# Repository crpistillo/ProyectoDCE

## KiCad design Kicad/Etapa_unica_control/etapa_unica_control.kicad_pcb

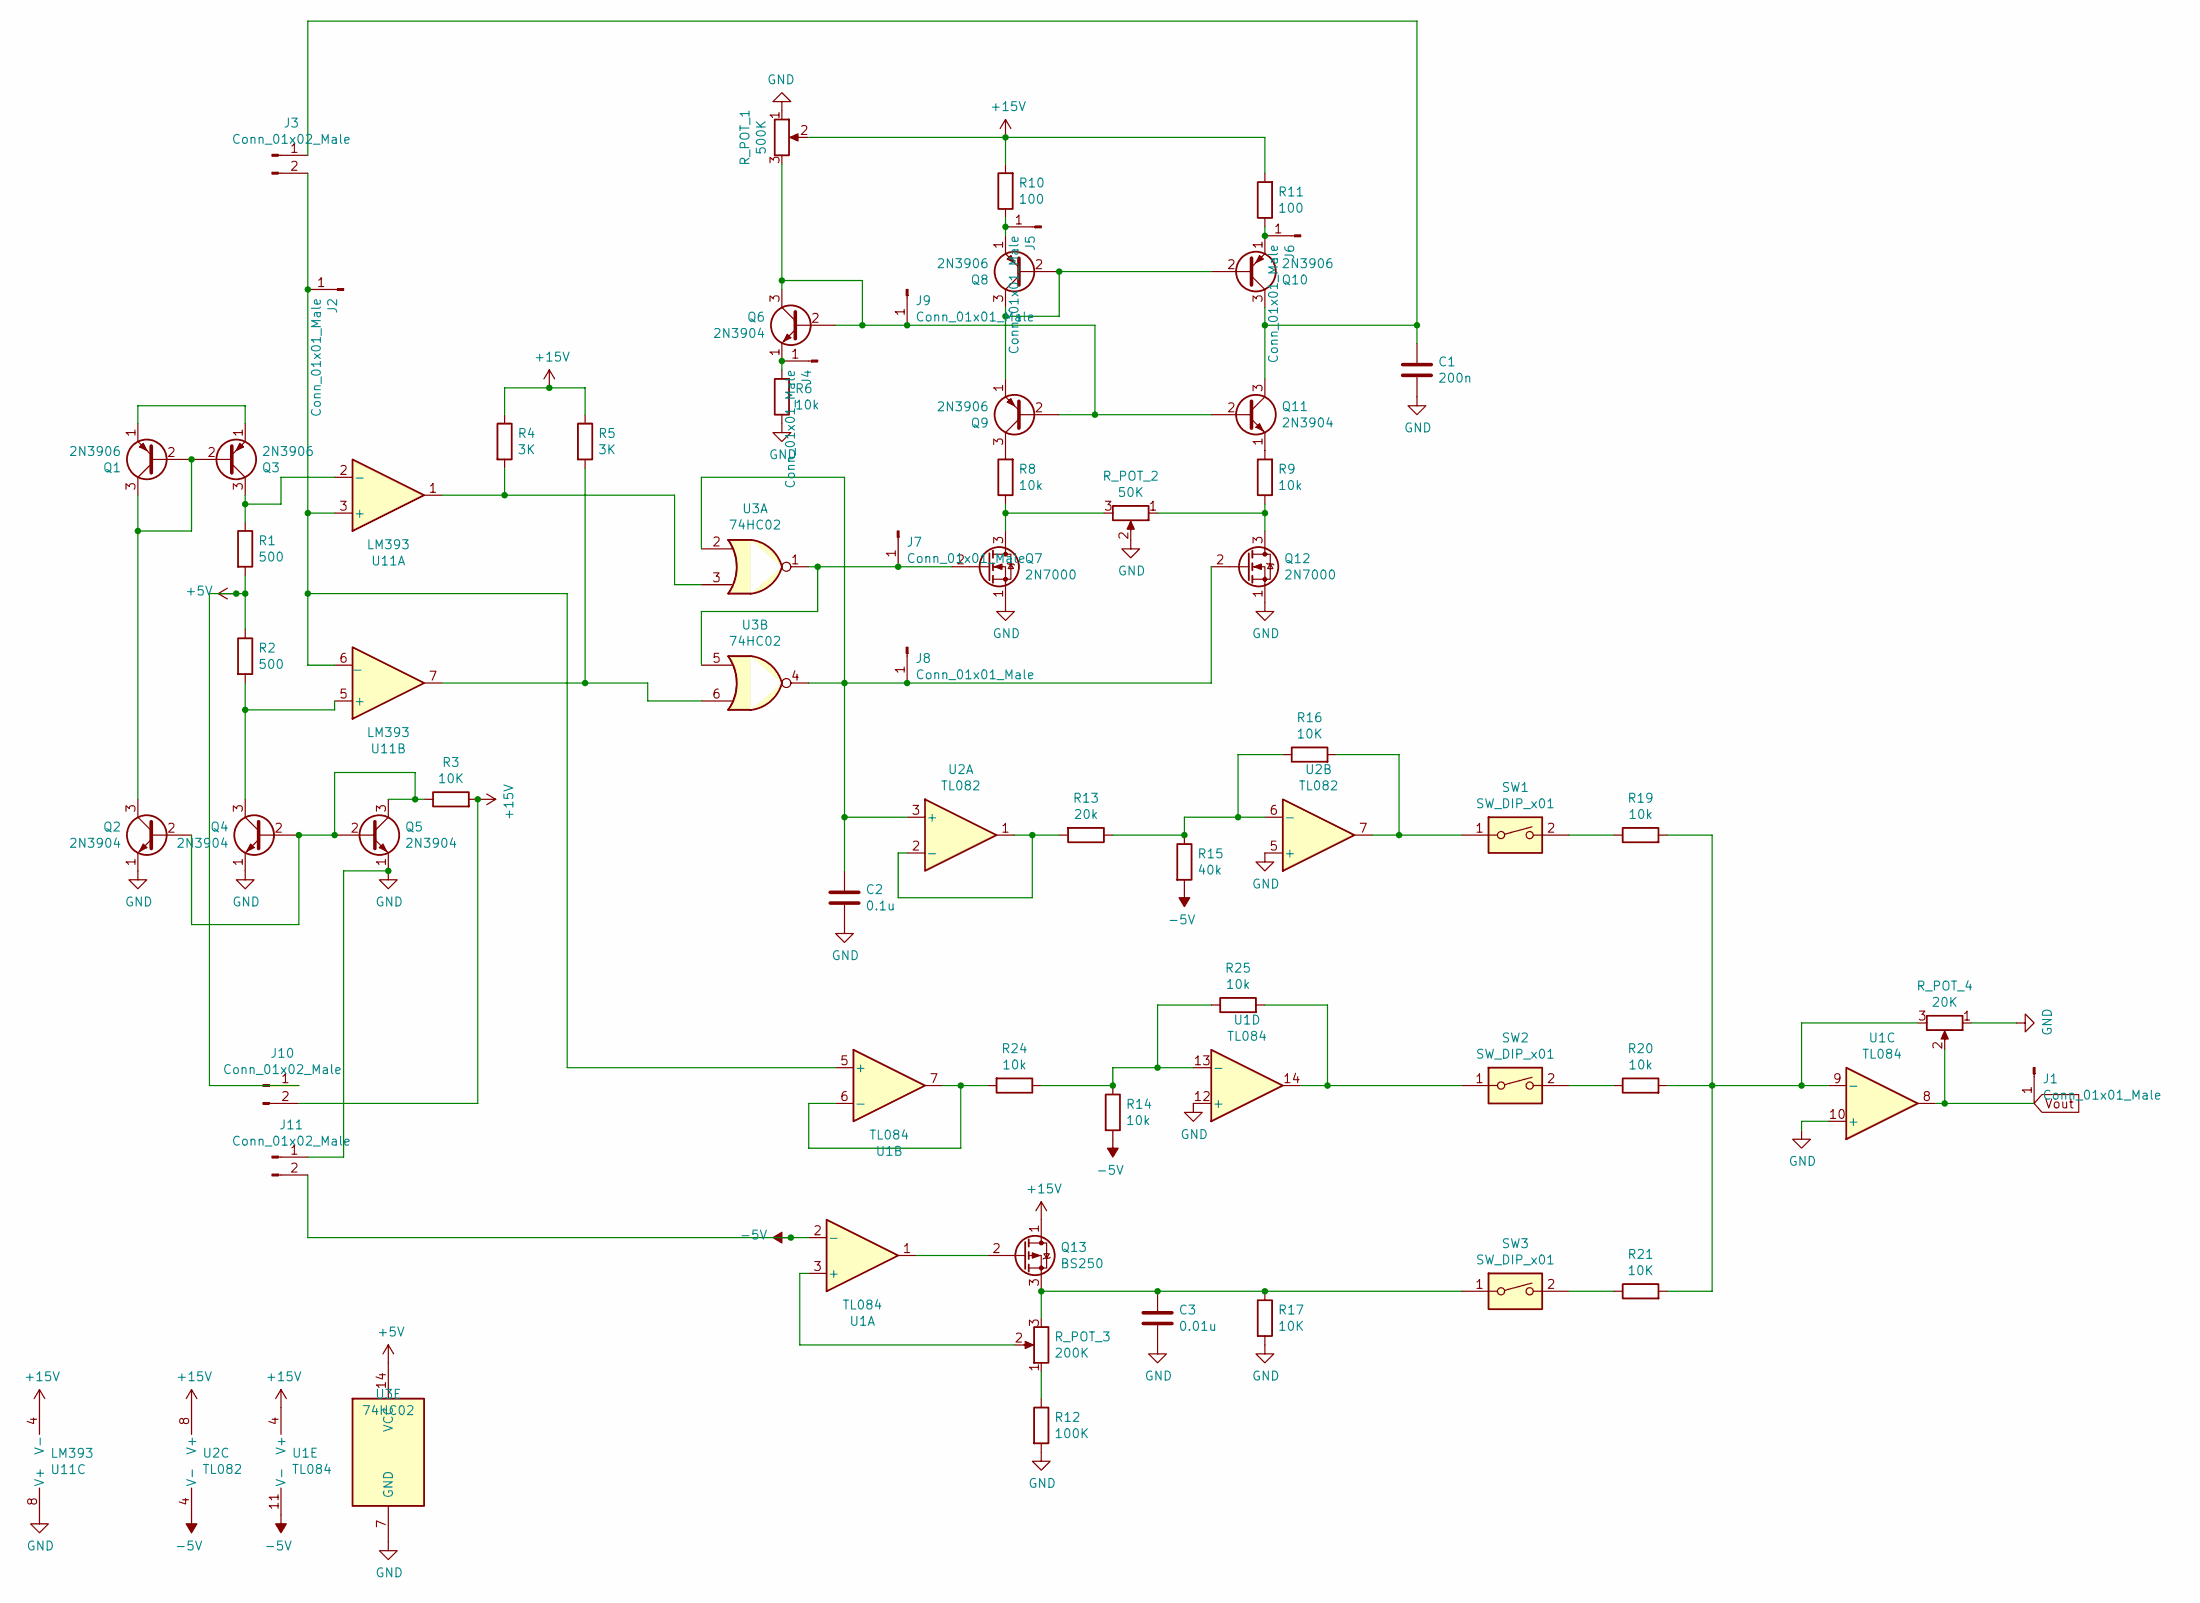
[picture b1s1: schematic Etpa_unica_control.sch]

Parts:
C1: 200n; C_Disc_D3.8mm_W2.6mm_P2.50mm
C2: 0.1u; C_Disc_D3.8mm_W2.6mm_P2.50mm
C3: 0.01u; C_Disc_D3.8mm_W2.6mm_P2.50mm
J1, J2, J4, J5, J6, J7, J8, J9: Conn_01x01_Male; PinHeader_1x01_P1.00mm_Vertical
J3, J10, J11: Conn_01x02_Male; PinHeader_1x02_P1.00mm_Vertical
Q1, Q3, Q8, Q9, Q10: 2N3906; TO-92_Inline
Q2, Q4, Q5, Q6, Q11: 2N3904; TO-92_Inline
Q7, Q12: 2N7000; TO-92_Inline
Q13: BS250; TO-92_Inline
R1, R2: 500; R_0603_1608Metric
R3, R16, R17, R21: 10K; R_0603_1608Metric
R4, R5: 3K; R_0603_1608Metric
R6, R8, R9, R14, R19, R20, R24, R25: 10k; R_0603_1608Metric
R10, R11: 100; R_0603_1608Metric
R12: 100K; R_0603_1608Metric
R13: 20k; R_0603_1608Metric
R15: 40k; R_0603_1608Metric
R_POT_1: 500K; Potentiometer_Bourns_3296W_Vertical
R_POT_2: 50K; Potentiometer_Bourns_3296W_Vertical
R_POT_3: 200K; Potentiometer_Bourns_3296W_Vertical
R_POT_4: 20K; Potentiometer_Bourns_3296W_Vertical
SW1, SW2, SW3: SW_DIP_x01; SW_PUSH_6mm
U1: TL084; SOIC-14W_7.5x9mm_P1.27mm
U2: TL082; DIP-8_W7.62mm
U3: 74HC02; DIP-14_W7.62mm
U11: LM393; DIP-8_W10.16mm

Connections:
+5V: J10.1, R1.2, R2.1, U3.14 (VCC)
+15V: J10.2, Q13.1 (D), R3.2, R4.1, R5.1, R10.2, R11.2, R_POT_1.2, U1.4 (V+), U2.8 (V+), U11.4 (V-)
-5V: J11.2, R14.2, R15.2, U1.2 (-), U1.11 (V-), U2.4 (V-)
GND: C1.2, C2.2, C3.2, J11.1, Q2.1 (E), Q4.1 (E), Q5.1 (E), Q7.1 (S), Q12.1 (S), R6.1, R12.2, R17.2, R_POT_1.1, R_POT_2.2, R_POT_4.1, U1.10 (+), U1.12 (+), U2.5 (+), U3.7 (GND), U11.8 (V+)
unnamed: C1.1, J3.1, Q10.3 (C), Q11.3 (C)
unnamed: C2.1, J8.1, Q12.2 (G), U2.3 (+), U3.2, U3.4
unnamed: C3.1, Q13.3 (S), R17.1, R_POT_3.3, SW3.1
unnamed: J2.1, J3.2, U1.5 (+), U11.3 (+), U11.6 (_)
unnamed: J4.1, Q6.1 (E), R6.2
unnamed: J5.1, Q8.1 (E), R10.1
unnamed: J6.1, Q10.1 (E), R11.1
unnamed: J7.1, Q7.2 (G), U3.1, U3.5
unnamed: J9.1, Q6.2 (B), Q6.3 (C), Q9.2 (B), Q11.2 (B), R_POT_1.3
unnamed: Q1.1 (E), Q3.1 (E)
unnamed: Q1.2 (B), Q1.3 (C), Q2.3 (C), Q3.2 (B)
unnamed: Q2.2 (B), Q4.2 (B), Q5.2 (B), Q5.3 (C), R3.1
unnamed: Q3.3 (C), R1.1, U11.2 (-)
unnamed: Q4.3 (C), R2.2, U11.5 (+)
unnamed: Q7.3 (D), R8.1, R_POT_2.3
unnamed: Q9.3 (C), R8.2
unnamed: Q8.2 (B), Q8.3 (C), Q9.1 (E), Q10.2 (B)
unnamed: Q11.1 (E), R9.2
unnamed: Q12.3 (D), R9.1, R_POT_2.1
unnamed: Q13.2 (G), U1.1
unnamed: R4.2, U3.3, U11.1
unnamed: R5.2, U3.6, U11.7
unnamed: R12.1, R_POT_3.1
unnamed: R13.1, R15.1, R16.1, U2.6 (-)
unnamed: R13.2, U2.1, U2.2 (-)
unnamed: R14.1, R24.1, R25.1, U1.13 (-)
unnamed: R16.2, SW1.1, U2.7
unnamed: R19.1, SW1.2
unnamed: R19.2, R20.2, R21.2, R_POT_4.3, U1.9 (-)
unnamed: R20.1, SW2.2
unnamed: R21.1, SW3.2
unnamed: R24.2, U1.6 (-), U1.7
unnamed: R25.2, SW2.1, U1.14
unnamed: R_POT_3.2, U1.3 (+)
Vout: J1.1, R_POT_4.2, U1.8

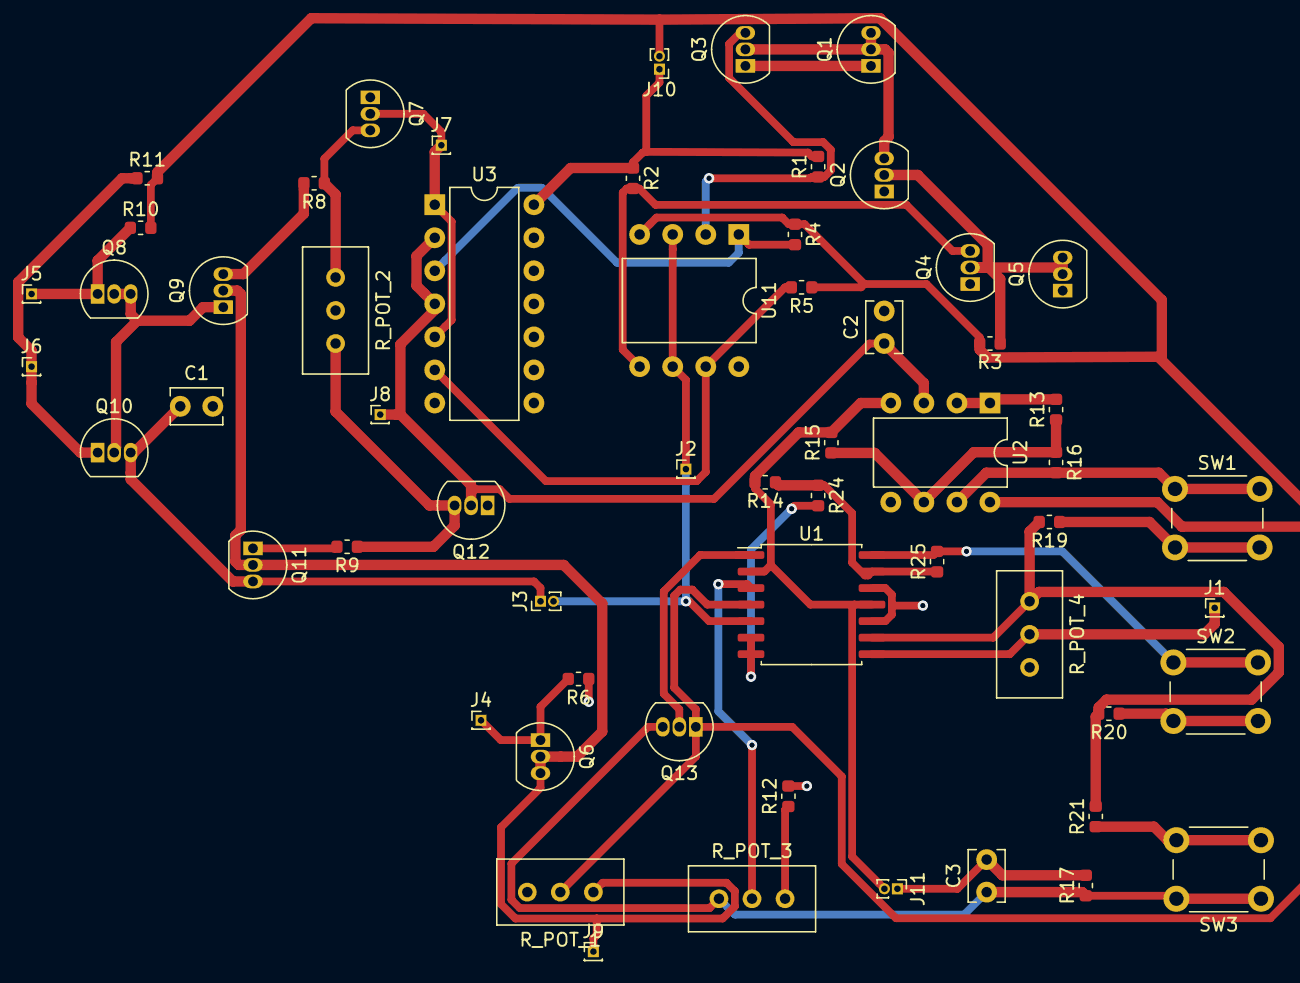
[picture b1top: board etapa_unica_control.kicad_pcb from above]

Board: 2 copper layers, 59 parts (0 on the bottom side), 39 nets.

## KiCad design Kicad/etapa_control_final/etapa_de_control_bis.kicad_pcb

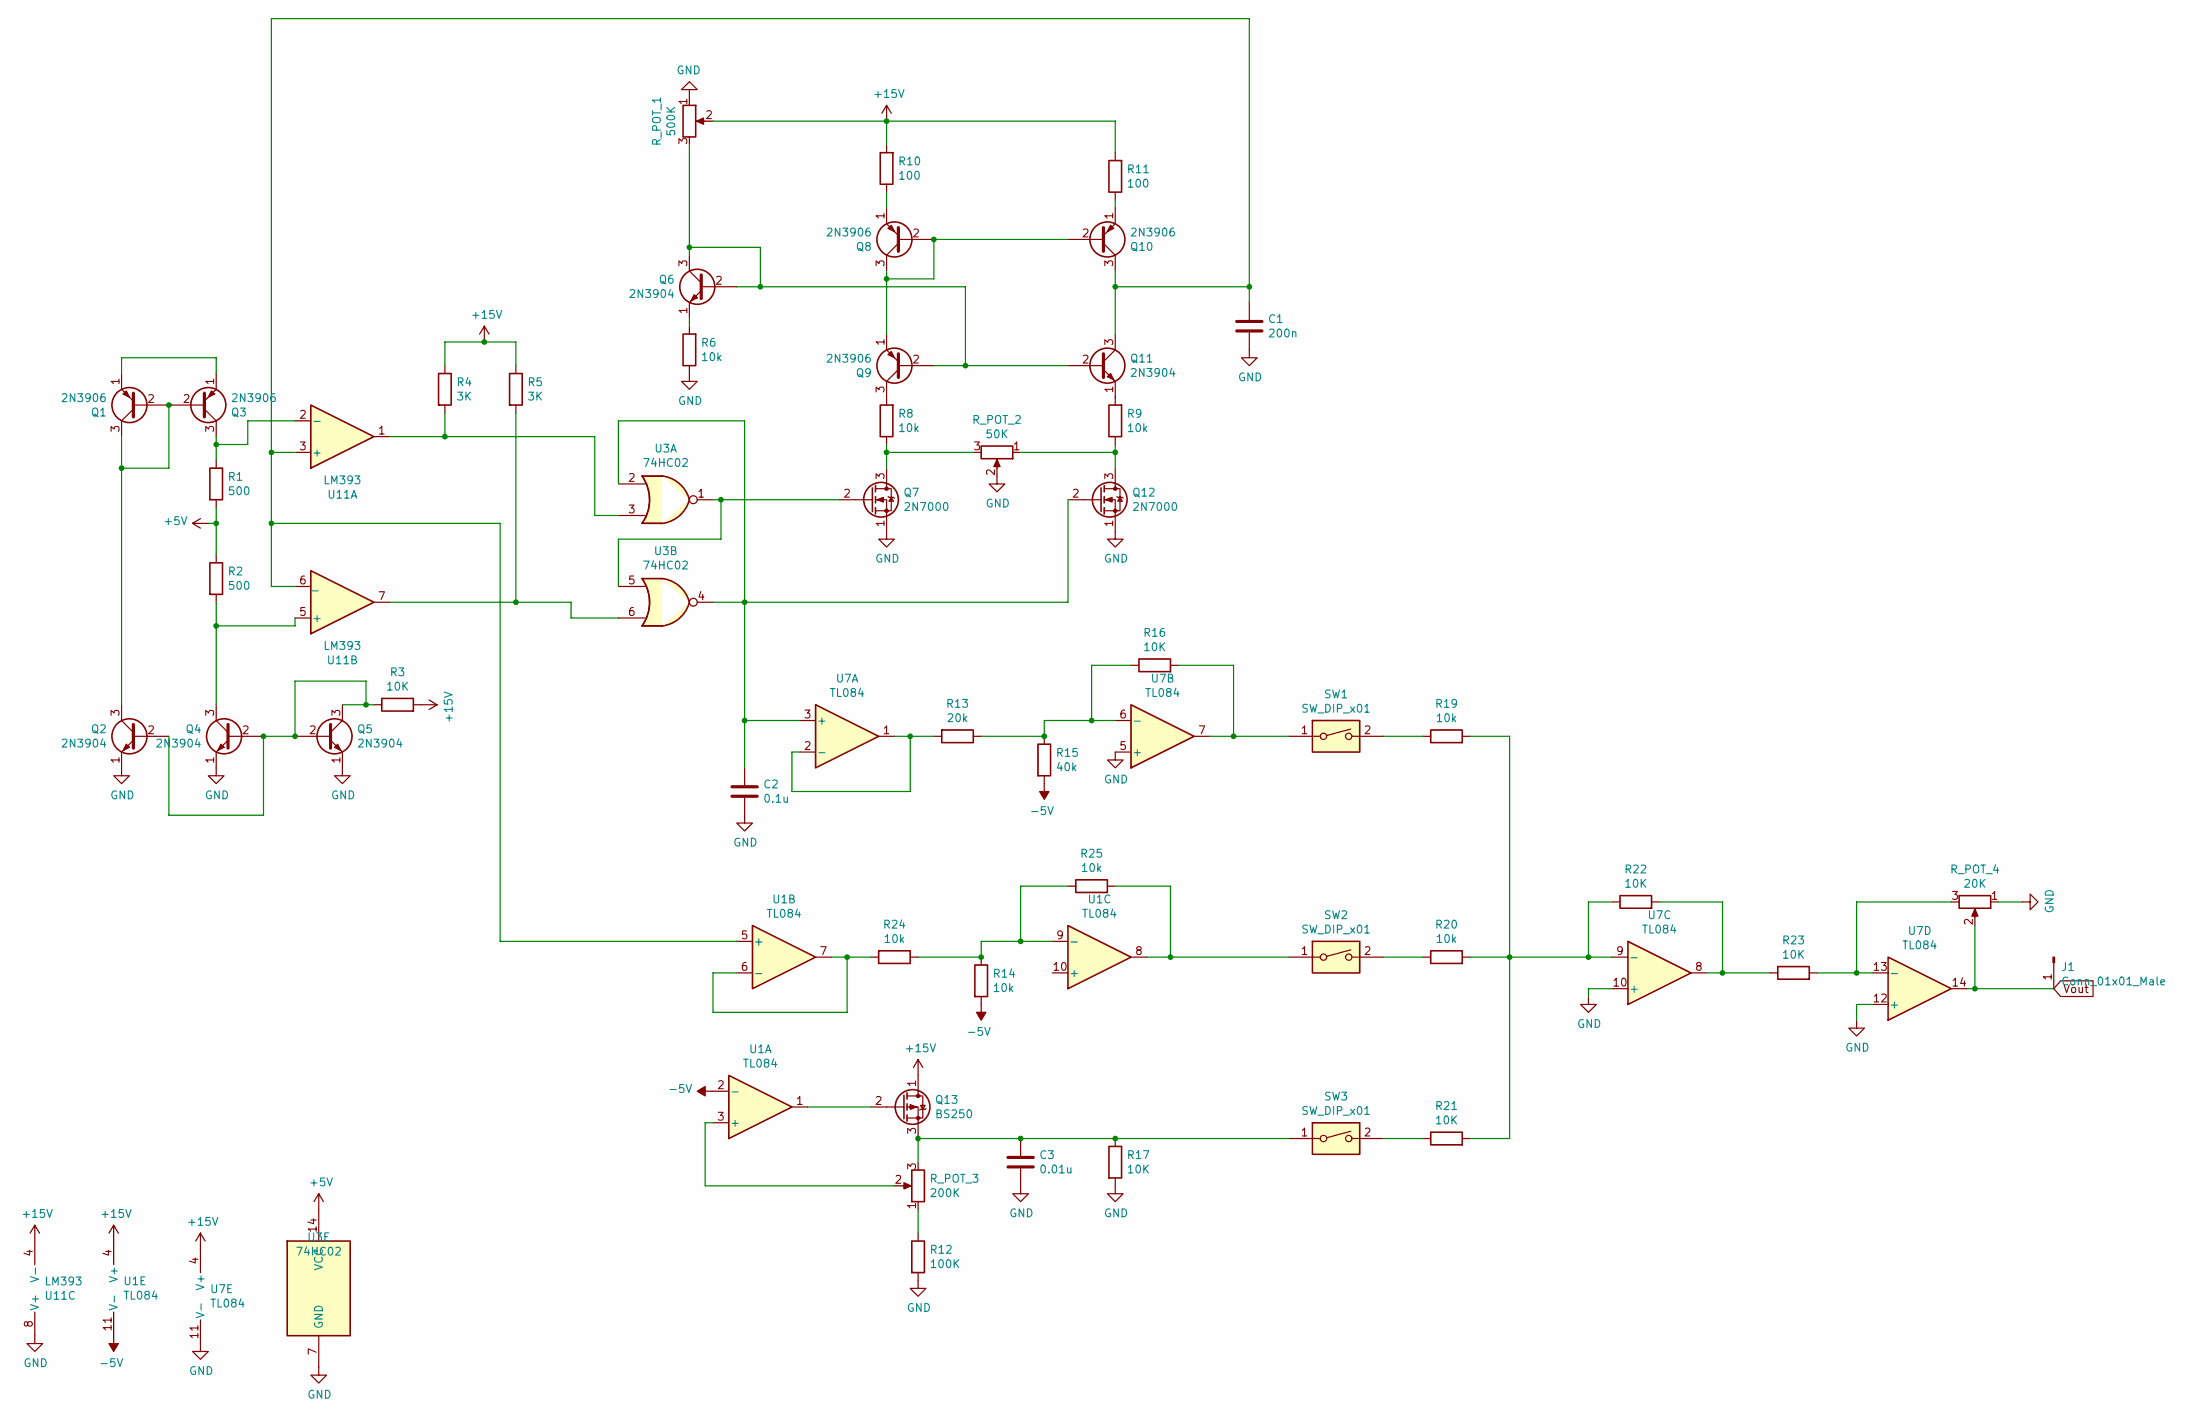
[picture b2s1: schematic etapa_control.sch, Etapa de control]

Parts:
C1: 200n; C_Disc_D3.8mm_W2.6mm_P2.50mm
C2: 0.1u; C_Disc_D3.8mm_W2.6mm_P2.50mm
C3: 0.01u; C_Disc_D3.8mm_W2.6mm_P2.50mm
J1: Conn_01x01_Male; PinHeader_1x01_P1.00mm_Vertical
Q1, Q3, Q8, Q9, Q10: 2N3906; TO-92_Inline
Q2, Q4, Q5, Q6, Q11: 2N3904; TO-92_Inline
Q7, Q12: 2N7000; TO-92_Inline
Q13: BS250; TO-92_Inline
R1, R2: 500; R_0603_1608Metric
R3, R16, R17, R21, R22, R23: 10K; R_0603_1608Metric
R4, R5: 3K; R_0603_1608Metric
R6, R8, R9, R14, R19, R20, R24, R25: 10k; R_0603_1608Metric
R10, R11: 100; R_0603_1608Metric
R12: 100K; R_0603_1608Metric
R13: 20k; R_0603_1608Metric
R15: 40k; R_0603_1608Metric
R_POT_1: 500K; Potentiometer_Bourns_3296W_Vertical
R_POT_2: 50K; Potentiometer_Bourns_3296W_Vertical
R_POT_3: 200K; Potentiometer_Bourns_3296W_Vertical
R_POT_4: 20K; Potentiometer_Bourns_3296W_Vertical
SW1, SW2, SW3: SW_DIP_x01; SW_PUSH_6mm
U1, U7: TL084; SOIC-14_3.9x8.7mm_P1.27mm
U3: 74HC02; SOIC-14_3.9x8.7mm_P1.27mm
U11: LM393; SOIC-8_3.9x4.9mm_P1.27mm

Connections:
+5V: R1.2, R2.1, U3.14 (VCC)
+15V: Q13.1 (D), R3.2, R4.1, R5.1, R10.2, R11.2, R_POT_1.2, U1.4 (V+), U7.4 (V+), U11.4 (V-); also elsewhere on the board
-5V: R14.2, R15.2, U1.2 (-), U1.11 (V-)
GND: C1.2, C2.2, C3.2, Q2.1 (E), Q4.1 (E), Q5.1 (E), Q7.1 (S), Q12.1 (S), R6.1, R12.2, R17.2, R_POT_1.1, R_POT_2.2, R_POT_4.1, U3.7 (GND), U7.5 (+), U7.10 (+), U7.11 (V-), U7.12 (+), U11.8 (V+); also elsewhere on the board
unnamed 4: R23.2, R_POT_4.3, U7.13 (-); also elsewhere on the board
unnamed 5: Q12.3 (D), R9.1, R_POT_2.1; also elsewhere on the board
unnamed 7: Q7.3 (D), R8.1, R_POT_2.3; also elsewhere on the board
unnamed 8: R12.1, R_POT_3.1; also elsewhere on the board
unnamed 9: R_POT_3.2, U1.3 (+); also elsewhere on the board
unnamed 10: C3.1, Q13.3 (S), R17.1, R_POT_3.3, SW3.1; also elsewhere on the board
unnamed: C1.1, Q10.3 (C), Q11.3 (C), U1.5 (+), U11.3 (+), U11.6 (_)
unnamed: C2.1, Q12.2 (G), U3.2, U3.4, U7.3 (+)
unnamed: Q1.1 (E), Q3.1 (E)
unnamed: Q1.2 (B), Q1.3 (C), Q2.3 (C), Q3.2 (B)
unnamed: Q2.2 (B), Q4.2 (B), Q5.2 (B), Q5.3 (C), R3.1
unnamed: Q3.3 (C), R1.1, U11.2 (-)
unnamed: Q4.3 (C), R2.2, U11.5 (+)
unnamed: Q6.1 (E), R6.2
unnamed: Q7.2 (G), U3.1, U3.5
unnamed: Q8.1 (E), R10.1
unnamed: Q9.3 (C), R8.2
unnamed: Q8.2 (B), Q8.3 (C), Q9.1 (E), Q10.2 (B)
unnamed: Q11.1 (E), R9.2
unnamed: Q6.2 (B), Q6.3 (C), Q9.2 (B), Q11.2 (B), R_POT_1.3
unnamed: Q13.2 (G), U1.1
unnamed: R4.2, U3.3, U11.1
unnamed: R5.2, U3.6, U11.7
unnamed: R13.1, R15.1, R16.1, U7.6 (-)
unnamed: R13.2, U7.1, U7.2 (-)
unnamed: R14.1, R24.1, R25.1, U1.9 (-)
unnamed: R16.2, SW1.1, U7.7
unnamed: R19.1, SW1.2
unnamed: R19.2, R20.2, R21.2, R22.1, U7.9 (-)
unnamed: R20.1, SW2.2
unnamed: R21.1, SW3.2
unnamed: R22.2, R23.1, U7.8
unnamed: R24.2, U1.6 (-), U1.7
unnamed: R25.2, SW2.1, U1.8
Vout: J1.1, R_POT_4.2, U7.14; also elsewhere on the board

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
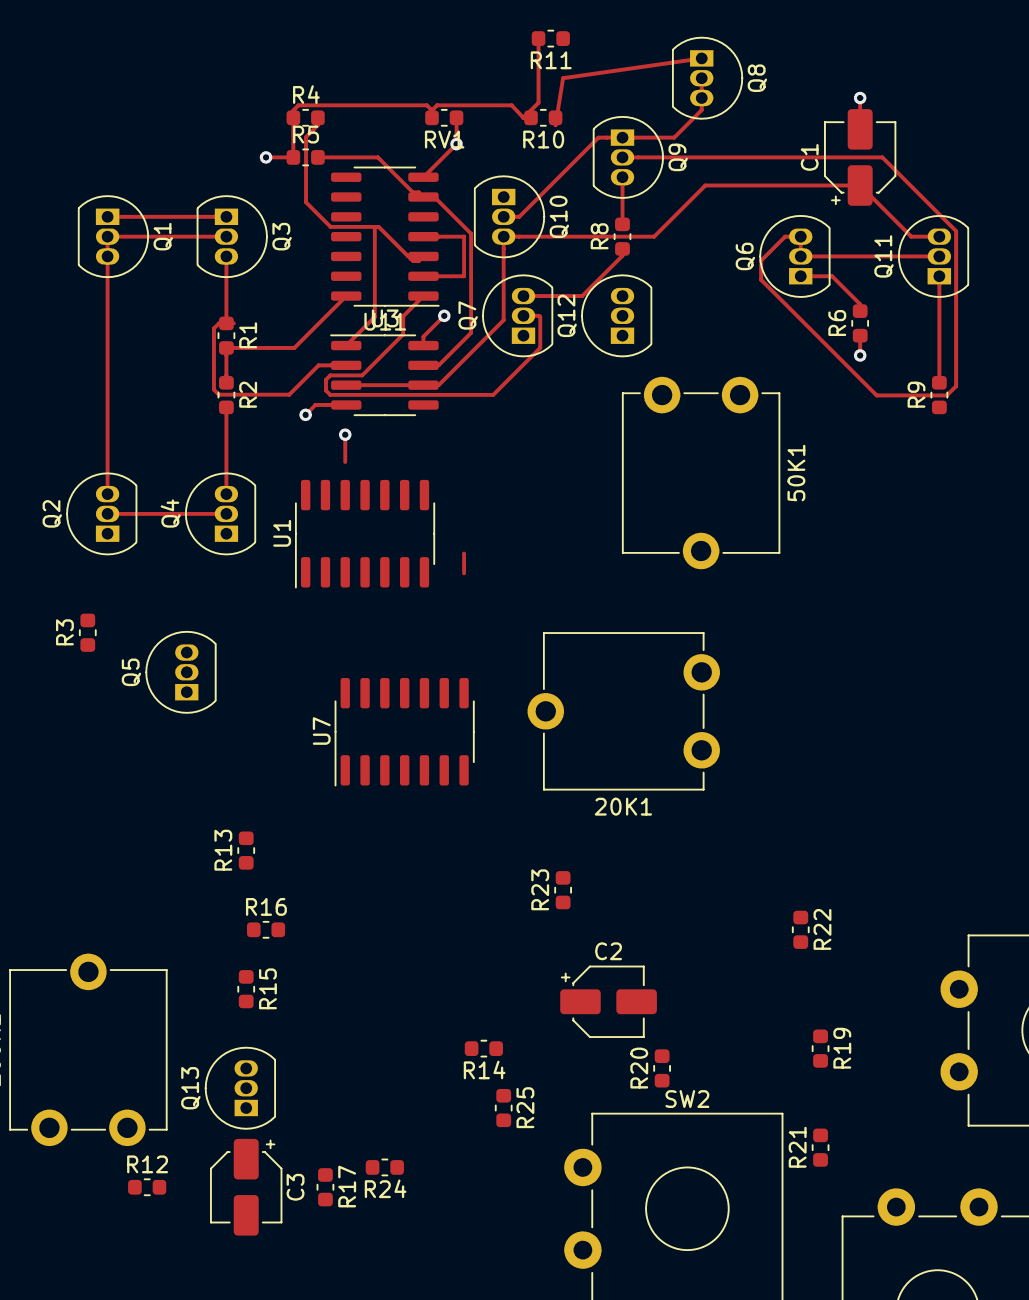
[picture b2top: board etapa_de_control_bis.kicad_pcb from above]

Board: 4 copper layers, 50 parts (0 on the bottom side), 39 nets.

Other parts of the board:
20K1, 50K1, 200K1: R_POT; Potentiometer_ACP_CA9-V10_Vertical
RV1: 500K; R_0603_1608Metric

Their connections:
+15V: RV1.2; also elsewhere on the board
GND: 20K1.1, RV1.1; also elsewhere on the board
unnamed 4: 20K1.3; also elsewhere on the board
unnamed 5: 50K1.1; also elsewhere on the board
unnamed 7: 50K1.3; also elsewhere on the board
unnamed 8: 200K1.1; also elsewhere on the board
unnamed 9: 200K1.2; also elsewhere on the board
unnamed 10: 200K1.3; also elsewhere on the board
Vout: 20K1.2; also elsewhere on the board
